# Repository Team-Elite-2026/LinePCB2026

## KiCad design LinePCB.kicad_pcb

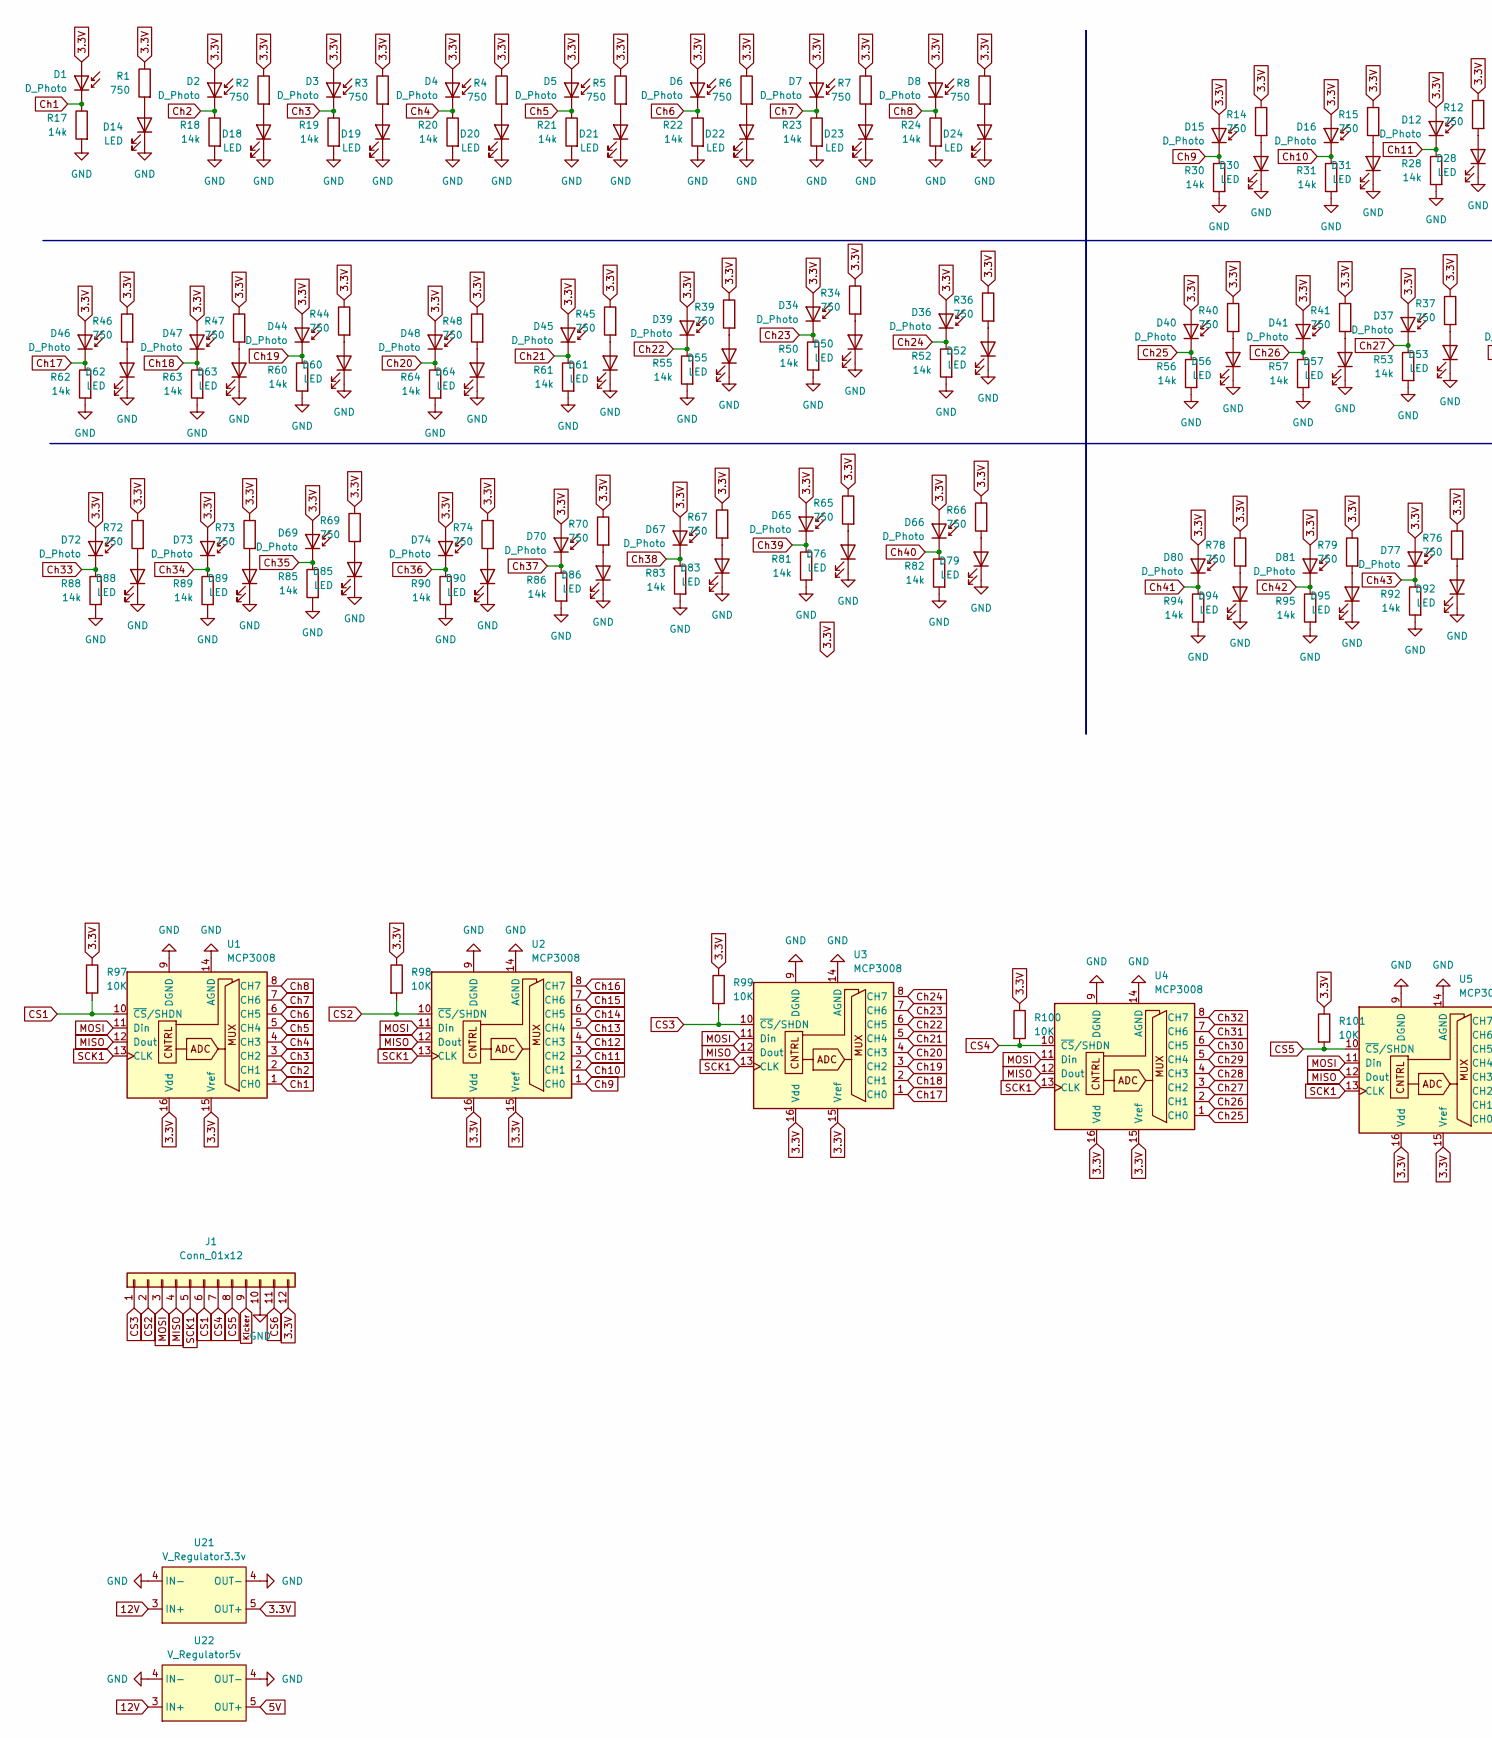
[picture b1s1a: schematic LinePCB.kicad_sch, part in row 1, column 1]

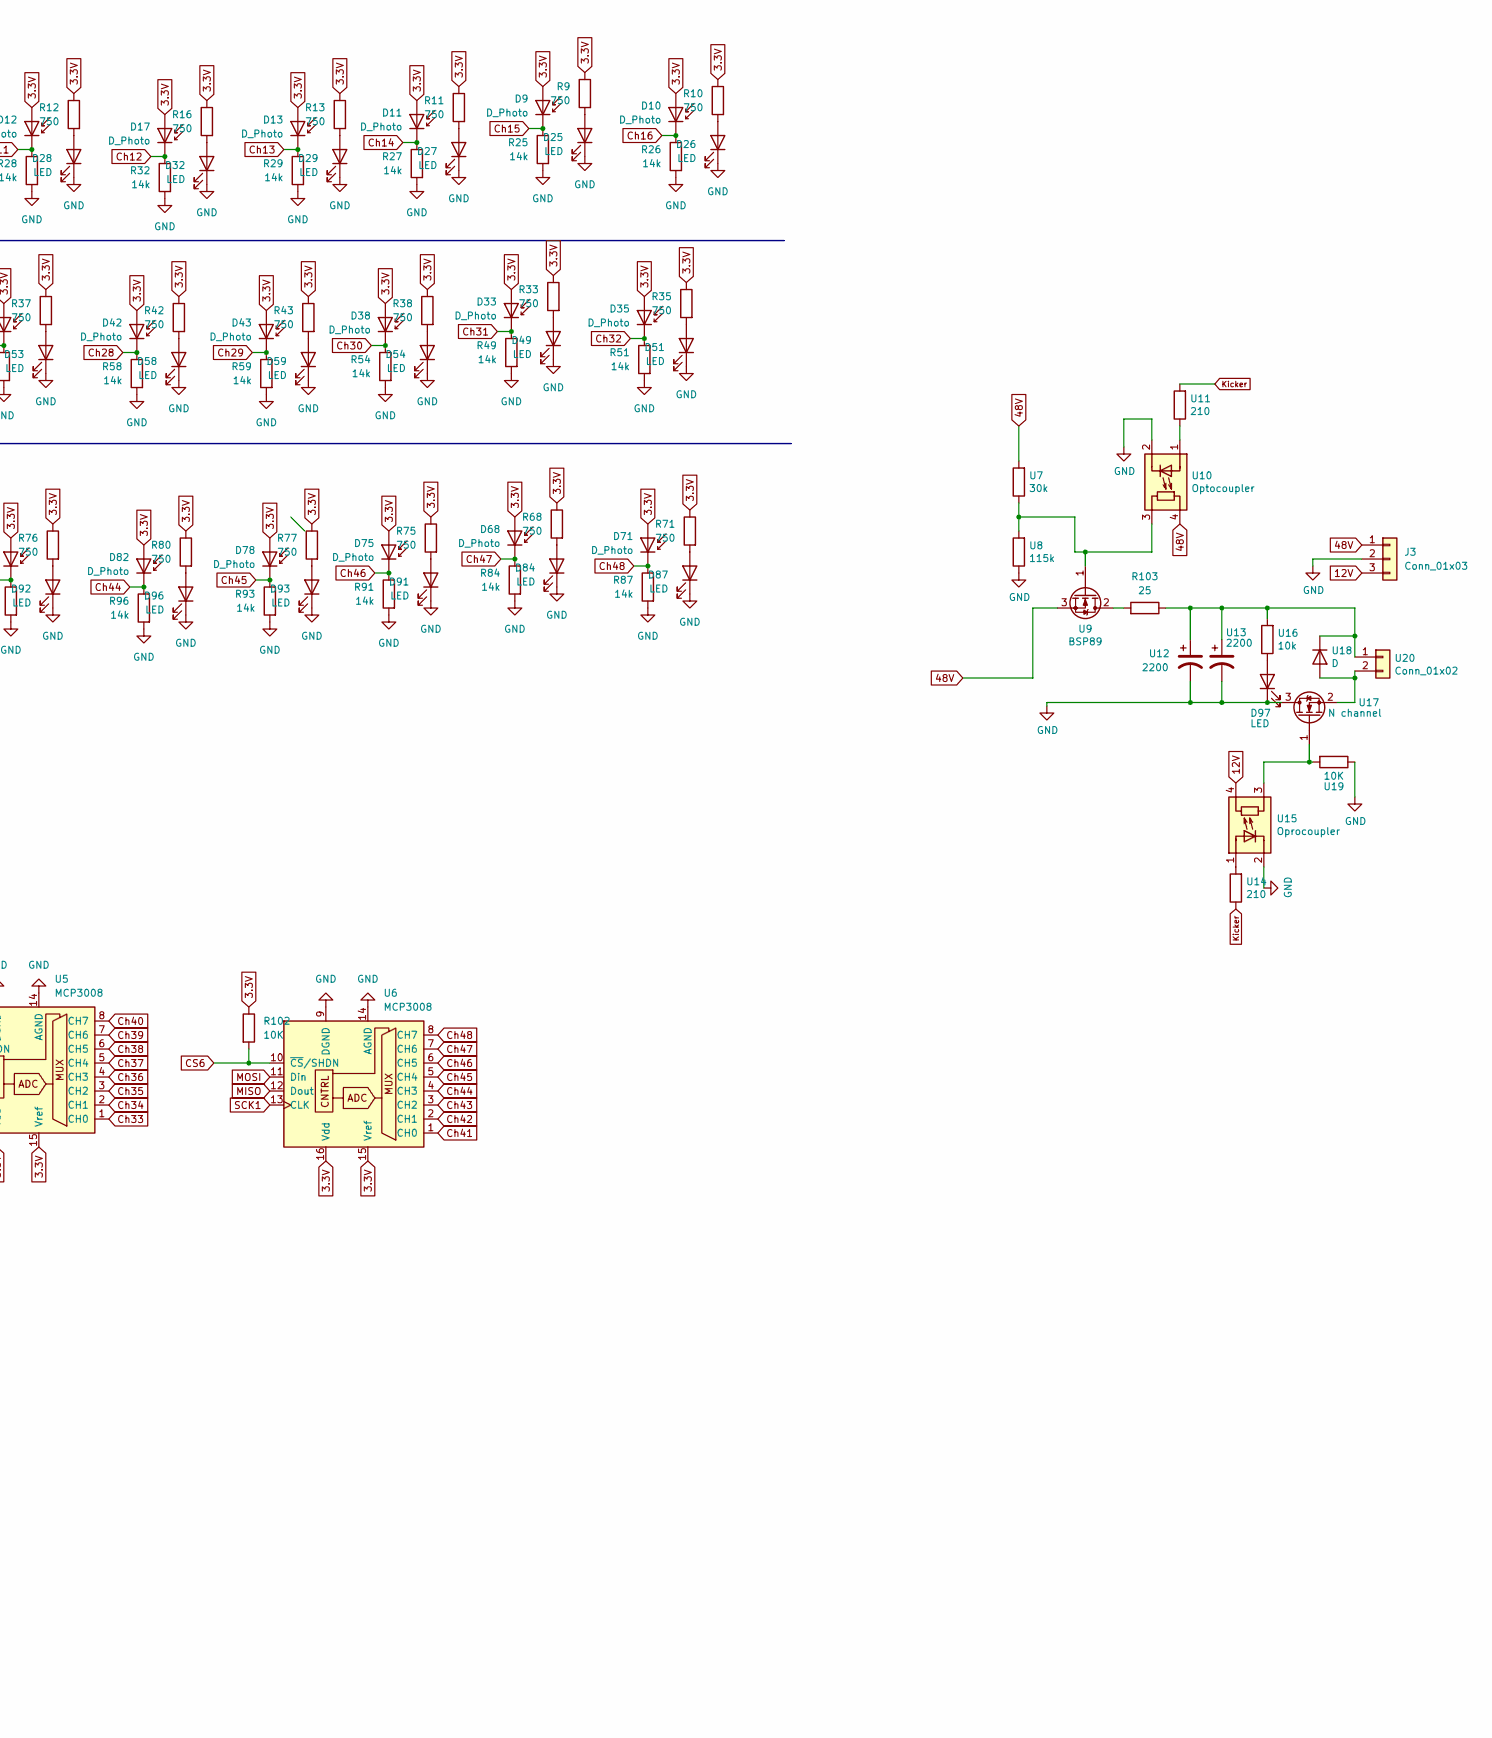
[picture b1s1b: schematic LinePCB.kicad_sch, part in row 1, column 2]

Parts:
D1, D2, D3, D4, D5, D6, D7, D8, D9, D10, D11, D12, D13, D15, D16, D17, D33, D34, D35, D36, D37, D38, D39, D40, D41, D42, D43, D44, D45, D46, D47, D48, D65, D66, D67, D68, D69, D70, D71, D72, D73, D74, D75, D77, D78, D80, D81, D82: D_Photo; D_0805_2012Metric_Pad1.15x1.40mm_HandSolder
D14, D18, D19, D20, D21, D22, D23, D24, D25, D26, D27, D28, D29, D30, D31, D32, D49, D50, D51, D52, D53, D54, D55, D56, D57, D58, D59, D60, D61, D62, D63, D64, D76, D79, D83, D84, D85, D86, D87, D88, D89, D90, D91, D92, D93, D94, D95, D96, D97: LED; LED_0805_2012Metric_Pad1.15x1.40mm_HandSolder
J1: Conn_01x12; IDC-Header_2x06_P2.54mm_Vertical
J3: Conn_01x03; JST_XH_B3B-XH-A_1x03_P2.50mm_Vertical
R1, R2, R3, R4, R5, R6, R7, R8, R9, R10, R11, R12, R13, R14, R15, R16, R33, R34, R35, R36, R37, R38, R39, R40, R41, R42, R43, R44, R45, R46, R47, R48, R65, R66, R67, R68, R69, R70, R71, R72, R73, R74, R75, R76, R77, R78, R79, R80: 750; R_0805_2012Metric_Pad1.20x1.40mm_HandSolder
R17, R18, R19, R20, R21, R22, R23, R24, R25, R26, R27, R28, R29, R30, R31, R32, R49, R50, R51, R52, R53, R54, R55, R56, R57, R58, R59, R60, R61, R62, R63, R64, R81, R82, R83, R84, R85, R86, R87, R88, R89, R90, R91, R92, R93, R94, R95, R96: 14k; R_0805_2012Metric_Pad1.20x1.40mm_HandSolder
R97, R98, R99, R100, R101, R102: 10K; R_0805_2012Metric_Pad1.20x1.40mm_HandSolder
R103: 25; TO-220-2_Vertical
U1, U2, U3, U4, U5, U6: MCP3008; SOIC16-N_MC_MCH-L
U7: 30k; R_0805_2012Metric_Pad1.20x1.40mm_HandSolder
U8: 115k; R_0805_2012Metric_Pad1.20x1.40mm_HandSolder
U9: BSP89; TO-220-3_Vertical
U10: Optocoupler; DIP-4_W7.62mm
U11, U14: 210; R_0805_2012Metric_Pad1.20x1.40mm_HandSolder
U12, U13: 2200; CP_Radial_D18.0mm_P7.50mm
U15: Oprocoupler; DIP-4_W7.62mm
U16: 10k; R_0805_2012Metric_Pad1.20x1.40mm_HandSolder
U17: N channel; TO-220-3_Vertical
U18: D; D_5W_P12.70mm_Horizontal
U19: 10K; R_0805_2012Metric_Pad1.20x1.40mm_HandSolder
U20: Conn_01x02; Pads
U21: V_Regulator3.3v; Pololu5V3.4A
U22: V_Regulator5v; Pololu5V3.4A

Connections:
3.3V: D1.2 (A), D2.2 (A), D3.2 (A), D4.2 (A), D5.2 (A), D6.2 (A), D7.2 (A), D8.2 (A), D9.2 (A), D10.2 (A), D11.2 (A), D12.2 (A), D13.2 (A), D15.2 (A), D16.2 (A), D17.2 (A), D33.2 (A), D34.2 (A), D35.2 (A), D36.2 (A), D37.2 (A), D38.2 (A), D39.2 (A), D40.2 (A), D41.2 (A), D42.2 (A), D43.2 (A), D44.2 (A), D45.2 (A), D46.2 (A), D47.2 (A), D48.2 (A), D65.2 (A), D66.2 (A), D67.2 (A), D68.2 (A), D69.2 (A), D70.2 (A), D71.2 (A), D72.2 (A), D73.2 (A), D74.2 (A), D75.2 (A), D77.2 (A), D78.2 (A), D80.2 (A), D81.2 (A), D82.2 (A), J1.12, R1.1, R2.1, R3.1, R4.1, R5.1, R6.1, R7.1, R8.1, R9.1, R10.1, R11.1, R12.1, R13.1, R14.1, R15.1, R16.1, R33.1, R34.1, R35.1, R36.1, R37.1, R38.1, R39.1, R40.1, R41.1, R42.1, R43.1, R44.1, R45.1, R46.1, R47.1, R48.1, R65.1, R66.1, R67.1, R68.1, R69.1, R70.1, R71.1, R72.1, R73.1, R74.1, R75.1, R76.1, R77.1, R78.1, R79.1, R80.1, R97.1, R98.1, R99.1, R100.1, R101.1, R102.1, U1.15 (Vref), U1.16 (Vdd), U2.15 (Vref), U2.16 (Vdd), U3.15 (Vref), U3.16 (Vdd), U4.15 (Vref), U4.16 (Vdd), U5.15 (Vref), U5.16 (Vdd), U6.15 (Vref), U6.16 (Vdd), U21.5 (OUT+); also elsewhere on the board
5V: U22.5 (OUT+); also elsewhere on the board
12V: J3.3, U15.4 (R), U21.3 (IN+), U22.3 (IN+); also elsewhere on the board
48V: J3.1, U7.2, U9.3 (S), U10.4 (R); also elsewhere on the board
CS1: J1.6, R97.2, U1.10 (~CS/SHDN)
CS2: J1.2, R98.2, U2.10 (~CS/SHDN)
CS3: J1.1, R99.2, U3.10 (~CS/SHDN)
CS4: J1.7, R100.2, U4.10 (~CS/SHDN)
CS5: J1.8, R101.2, U5.10 (~CS/SHDN)
CS6: J1.11, R102.2, U6.10 (~CS/SHDN)
Ch1: D1.1 (K), R17.1, U1.1 (CH0)
Ch2: D2.1 (K), R18.1, U1.2 (CH1)
Ch3: D3.1 (K), R19.1, U1.3 (CH2)
Ch4: D4.1 (K), R20.1, U1.4 (CH3)
Ch5: D5.1 (K), R21.1, U1.5 (CH4)
Ch6: D6.1 (K), R22.1, U1.6 (CH5)
Ch7: D7.1 (K), R23.1, U1.7 (CH6)
Ch8: D8.1 (K), R24.1, U1.8 (CH7)
Ch9: D15.1 (K), R30.1, U2.1 (CH0)
Ch10: D16.1 (K), R31.1, U2.2 (CH1)
Ch11: D12.1 (K), R28.1, U2.3 (CH2)
Ch12: D17.1 (K), R32.1, U2.4 (CH3)
Ch13: D13.1 (K), R29.1, U2.5 (CH4)
Ch14: D11.1 (K), R27.1, U2.6 (CH5)
Ch15: D9.1 (K), R25.1, U2.7 (CH6)
Ch16: D10.1 (K), R26.1, U2.8 (CH7)
Ch17: D46.1 (K), R62.1, U3.1 (CH0)
Ch18: D47.1 (K), R63.1, U3.2 (CH1)
Ch19: D44.1 (K), R60.1, U3.3 (CH2)
Ch20: D48.1 (K), R64.1, U3.4 (CH3)
Ch21: D45.1 (K), R61.1, U3.5 (CH4)
Ch22: D39.1 (K), R55.1, U3.6 (CH5)
Ch23: D34.1 (K), R50.1, U3.7 (CH6)
Ch24: D36.1 (K), R52.1, U3.8 (CH7)
Ch25: D40.1 (K), R56.1, U4.1 (CH0)
Ch26: D41.1 (K), R57.1, U4.2 (CH1)
Ch27: D37.1 (K), R53.1, U4.3 (CH2)
Ch28: D42.1 (K), R58.1, U4.4 (CH3)
Ch29: D43.1 (K), R59.1, U4.5 (CH4)
Ch30: D38.1 (K), R54.1, U4.6 (CH5)
Ch31: D33.1 (K), R49.1, U4.7 (CH6)
Ch32: D35.1 (K), R51.1, U4.8 (CH7)
Ch33: D72.1 (K), R88.1, U5.1 (CH0)
Ch34: D73.1 (K), R89.1, U5.2 (CH1)
Ch35: D69.1 (K), R85.1, U5.3 (CH2)
Ch36: D74.1 (K), R90.1, U5.4 (CH3)
Ch37: D70.1 (K), R86.1, U5.5 (CH4)
Ch38: D67.1 (K), R83.1, U5.6 (CH5)
Ch39: D65.1 (K), R81.1, U5.7 (CH6)
Ch40: D66.1 (K), R82.1, U5.8 (CH7)
Ch41: D80.1 (K), R94.1, U6.1 (CH0)
Ch42: D81.1 (K), R95.1, U6.2 (CH1)
Ch43: D77.1 (K), R92.1, U6.3 (CH2)
Ch44: D82.1 (K), R96.1, U6.4 (CH3)
Ch45: D78.1 (K), R93.1, U6.5 (CH4)
Ch46: D75.1 (K), R91.1, U6.6 (CH5)
Ch47: D68.1 (K), R84.1, U6.7 (CH6)
Ch48: D71.1 (K), R87.1, U6.8 (CH7)
GND: D14.1 (K), D18.1 (K), D19.1 (K), D20.1 (K), D21.1 (K), D22.1 (K), D23.1 (K), D24.1 (K), D25.1 (K), D26.1 (K), D27.1 (K), D28.1 (K), D29.1 (K), D30.1 (K), D31.1 (K), D32.1 (K), D49.1 (K), D50.1 (K), D51.1 (K), D52.1 (K), D53.1 (K), D54.1 (K), D55.1 (K), D56.1 (K), D57.1 (K), D58.1 (K), D59.1 (K), D60.1 (K), D61.1 (K), D62.1 (K), D63.1 (K), D64.1 (K), D76.1 (K), D79.1 (K), D83.1 (K), D84.1 (K), D85.1 (K), D86.1 (K), D87.1 (K), D88.1 (K), D89.1 (K), D90.1 (K), D91.1 (K), D92.1 (K), D93.1 (K), D94.1 (K), D95.1 (K), D96.1 (K), D97.1 (K), J1.10, J3.2, R17.2, R18.2, R19.2, R20.2, R21.2, R22.2, R23.2, R24.2, R25.2, R26.2, R27.2, R28.2, R29.2, R30.2, R31.2, R32.2, R49.2, R50.2, R51.2, R52.2, R53.2, R54.2, R55.2, R56.2, R57.2, R58.2, R59.2, R60.2, R61.2, R62.2, R63.2, R64.2, R81.2, R82.2, R83.2, R84.2, R85.2, R86.2, R87.2, R88.2, R89.2, R90.2, R91.2, R92.2, R93.2, R94.2, R95.2, R96.2, U1.9 (DGND), U1.14 (AGND), U2.9 (DGND), U2.14 (AGND), U3.9 (DGND), U3.14 (AGND), U4.9 (DGND), U4.14 (AGND), U5.9 (DGND), U5.14 (AGND), U6.9 (DGND), U6.14 (AGND), U8.1, U10.2 (K), U12.2, U13.2, U15.2 (K), U17.3 (D), U19.1, U21.4 (IN-), U22.4 (OUT-); also elsewhere on the board
Kicker: J1.9, U11.2, U14.1
MISO: J1.4, U1.12 (Dout), U2.12 (Dout), U3.12 (Dout), U4.12 (Dout), U5.12 (Dout), U6.12 (Dout)
MOSI: J1.3, U1.11 (Din), U2.11 (Din), U3.11 (Din), U4.11 (Din), U5.11 (Din), U6.11 (Din)
unnamed: D14.2 (A), R1.2
unnamed: D18.2 (A), R2.2
unnamed: D19.2 (A), R3.2
unnamed: D20.2 (A), R4.2
unnamed: D21.2 (A), R5.2
unnamed: D22.2 (A), R6.2
unnamed: D23.2 (A), R7.2
unnamed: D24.2 (A), R8.2
unnamed: D25.2 (A), R9.2
unnamed: D26.2 (A), R10.2
unnamed: D27.2 (A), R11.2
unnamed: D28.2 (A), R12.2
unnamed: D29.2 (A), R13.2
unnamed: D30.2 (A), R14.2
unnamed: D31.2 (A), R15.2
unnamed: D32.2 (A), R16.2
unnamed: D49.2 (A), R33.2
unnamed: D50.2 (A), R34.2
unnamed: D51.2 (A), R35.2
unnamed: D52.2 (A), R36.2
unnamed: D53.2 (A), R37.2
unnamed: D54.2 (A), R38.2
unnamed: D55.2 (A), R39.2
unnamed: D56.2 (A), R40.2
unnamed: D57.2 (A), R41.2
unnamed: D58.2 (A), R42.2
unnamed: D59.2 (A), R43.2
unnamed: D60.2 (A), R44.2
unnamed: D61.2 (A), R45.2
unnamed: D62.2 (A), R46.2
unnamed: D63.2 (A), R47.2
unnamed: D64.2 (A), R48.2
unnamed: D76.2 (A), R65.2
unnamed: D79.2 (A), R66.2
unnamed: D83.2 (A), R67.2
unnamed: D84.2 (A), R68.2
unnamed: D85.2 (A), R69.2
unnamed: D86.2 (A), R70.2
unnamed: D87.2 (A), R71.2
unnamed: D88.2 (A), R72.2
unnamed: D89.2 (A), R73.2
unnamed: D90.2 (A), R74.2
unnamed: D91.2 (A), R75.2
unnamed: D92.2 (A), R76.2
unnamed: D93.2 (A), R77.2
unnamed: D94.2 (A), R78.2
unnamed: D95.2 (A), R79.2
unnamed: D96.2 (A), R80.2
unnamed: D97.2 (A), U16.1
unnamed: R103.2, U9.2 (D)
unnamed: U7.1, U8.2, U9.1 (G), U10.3 (R)
unnamed: U10.1 (A), U11.1
unnamed: U14.2, U15.1 (A)
unnamed: U15.3 (R), U17.1 (G), U19.2
unnamed: U17.2 (S), U18.2 (A), U20.2
unnamed: R103.1, U12.1, U13.1, U16.2, U18.1 (K), U20.1
SCK1: J1.5, U1.13 (CLK), U2.13 (CLK), U3.13 (CLK), U4.13 (CLK), U5.13 (CLK), U6.13 (CLK)

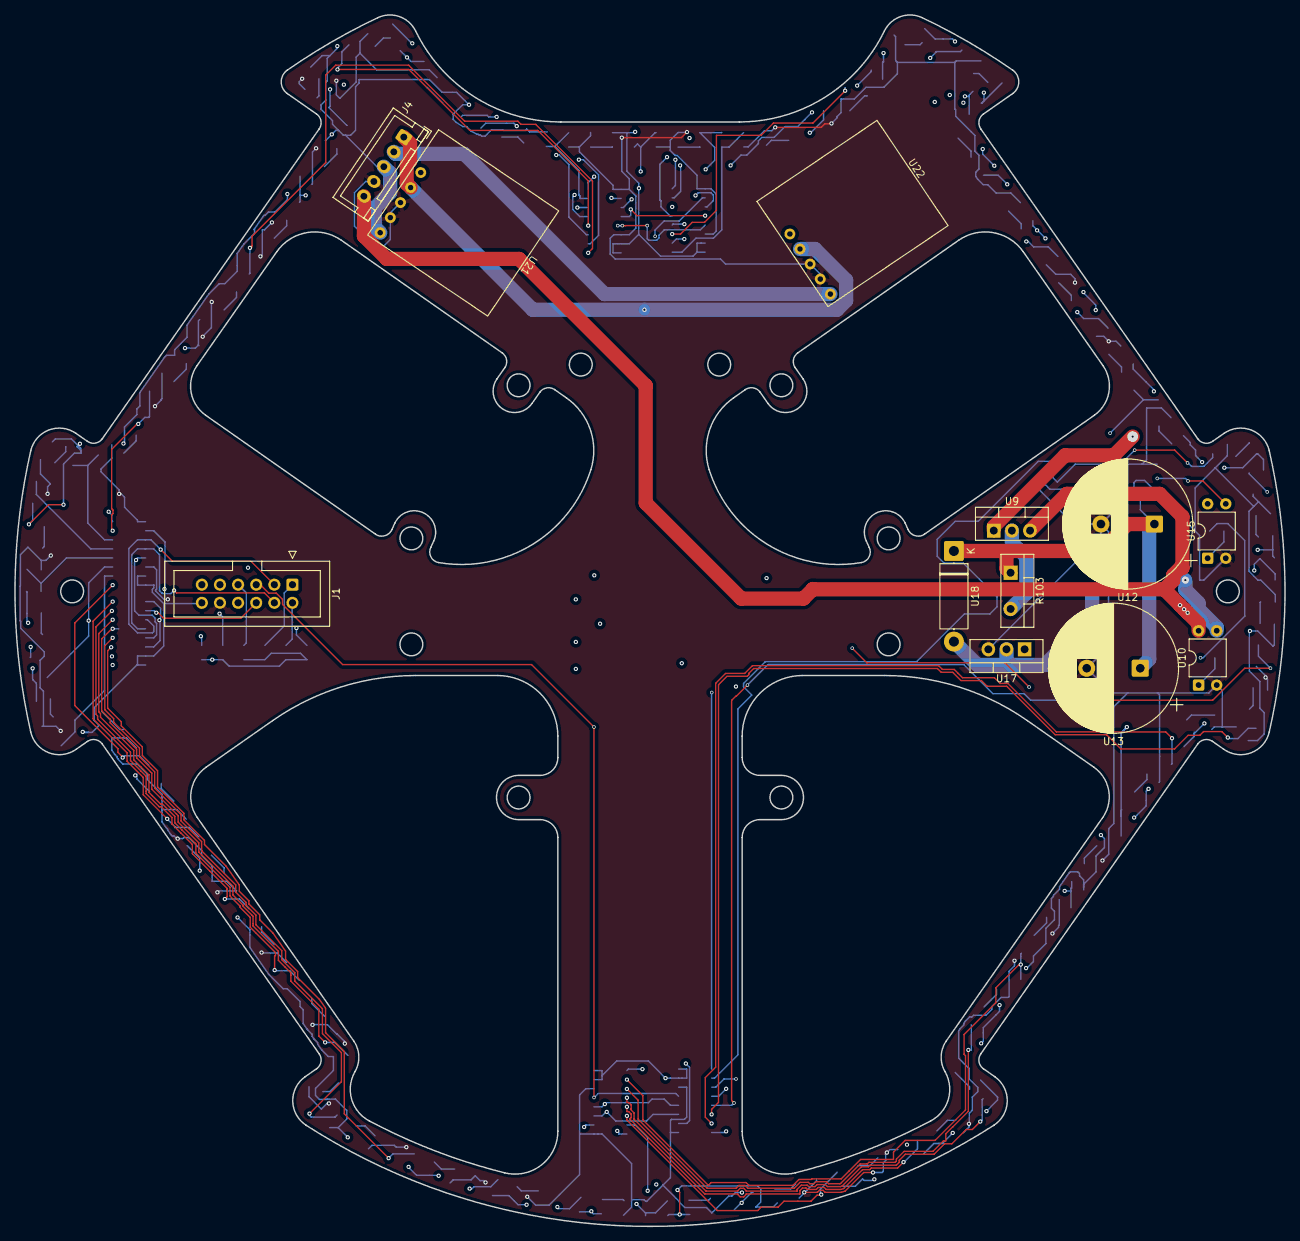
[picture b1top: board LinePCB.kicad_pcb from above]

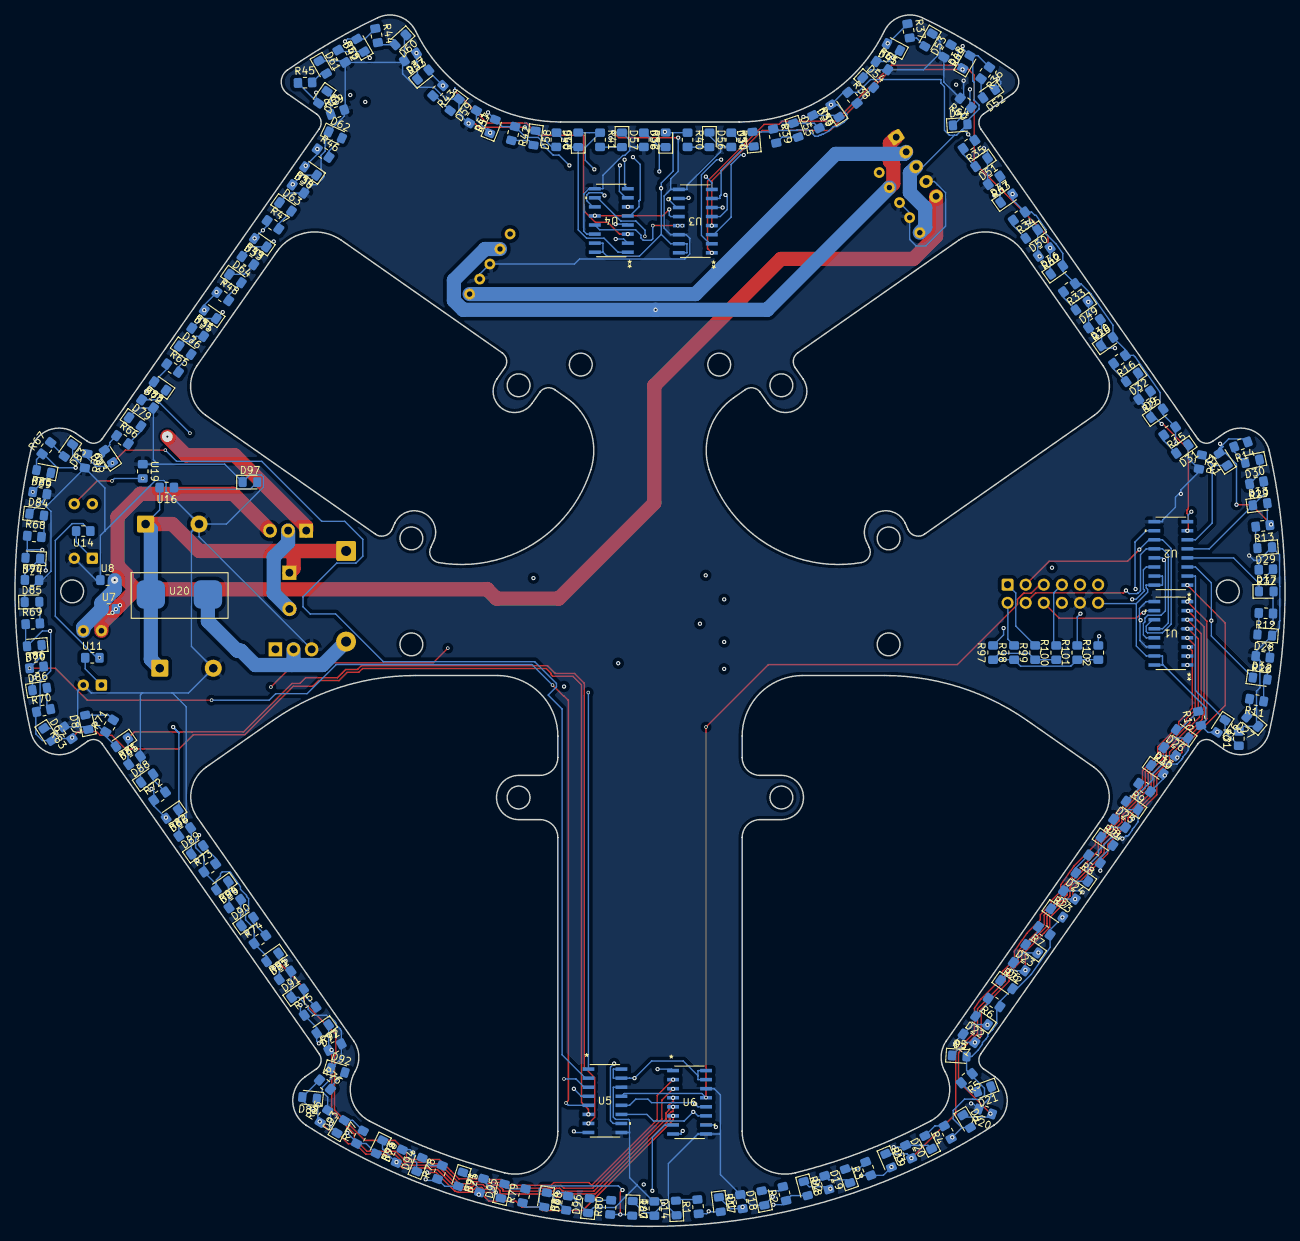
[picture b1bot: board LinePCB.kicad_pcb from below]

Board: 4 copper layers, 178.0 x 169.8 mm, 224 parts (212 on the bottom side), 119 nets.

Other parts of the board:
J4: Conn_01x05_Pin; JST_XH_B5B-XH-A_1x05_P2.50mm_Vertical

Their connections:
3.3V: J4.3; also elsewhere on the board
5V: J4.2; also elsewhere on the board
12V: J4.1; also elsewhere on the board
48V: J4.5; also elsewhere on the board
GND: J4.4; also elsewhere on the board

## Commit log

2025-08-17 Schematic Done
2025-08-17 Placement Finished
2025-08-27 Placement
2025-08-27 Finished routing, needs clearing up clearance errors
2025-08-28 Done
2026-03-17 added voltage reg
2026-03-17 rotated everything
2026-03-22 Added JST
2026-03-25 re routed and added voltage
2026-03-25 mb didnt save some
2026-03-25 Fixed Routing Errors
2026-03-25 Fixed Floating Ground
